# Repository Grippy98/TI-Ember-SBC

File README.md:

# TI-Ember-SBC

[Work in Progress Schematic](TI_Ember_SCH_V00.pdf)

### What is it?

An Arduino Portenta form-factor compatible board based around the Texas Instruments AM625 SiP (System in Package)

### What are the goals of the project?

  * To design a low cost, high performance Arduino Portenta MPU.
  * To help bridge the gap between MCUs and MPUs and create an easy path for projects to migrate to Linux
  * To showcase a 4-6 Layer design that is easily adaptable by the community, open source and built with KiCAD!

### What about software?
  * The board will ship with eMMC pre-flashed with Texas Instruments flavored Debian - traditional Yocto distro will also be available
  * Community engagement is encouraged, and OS Iamges can be flashed or loaded to the on-board eMMC storage or Micro SD Card

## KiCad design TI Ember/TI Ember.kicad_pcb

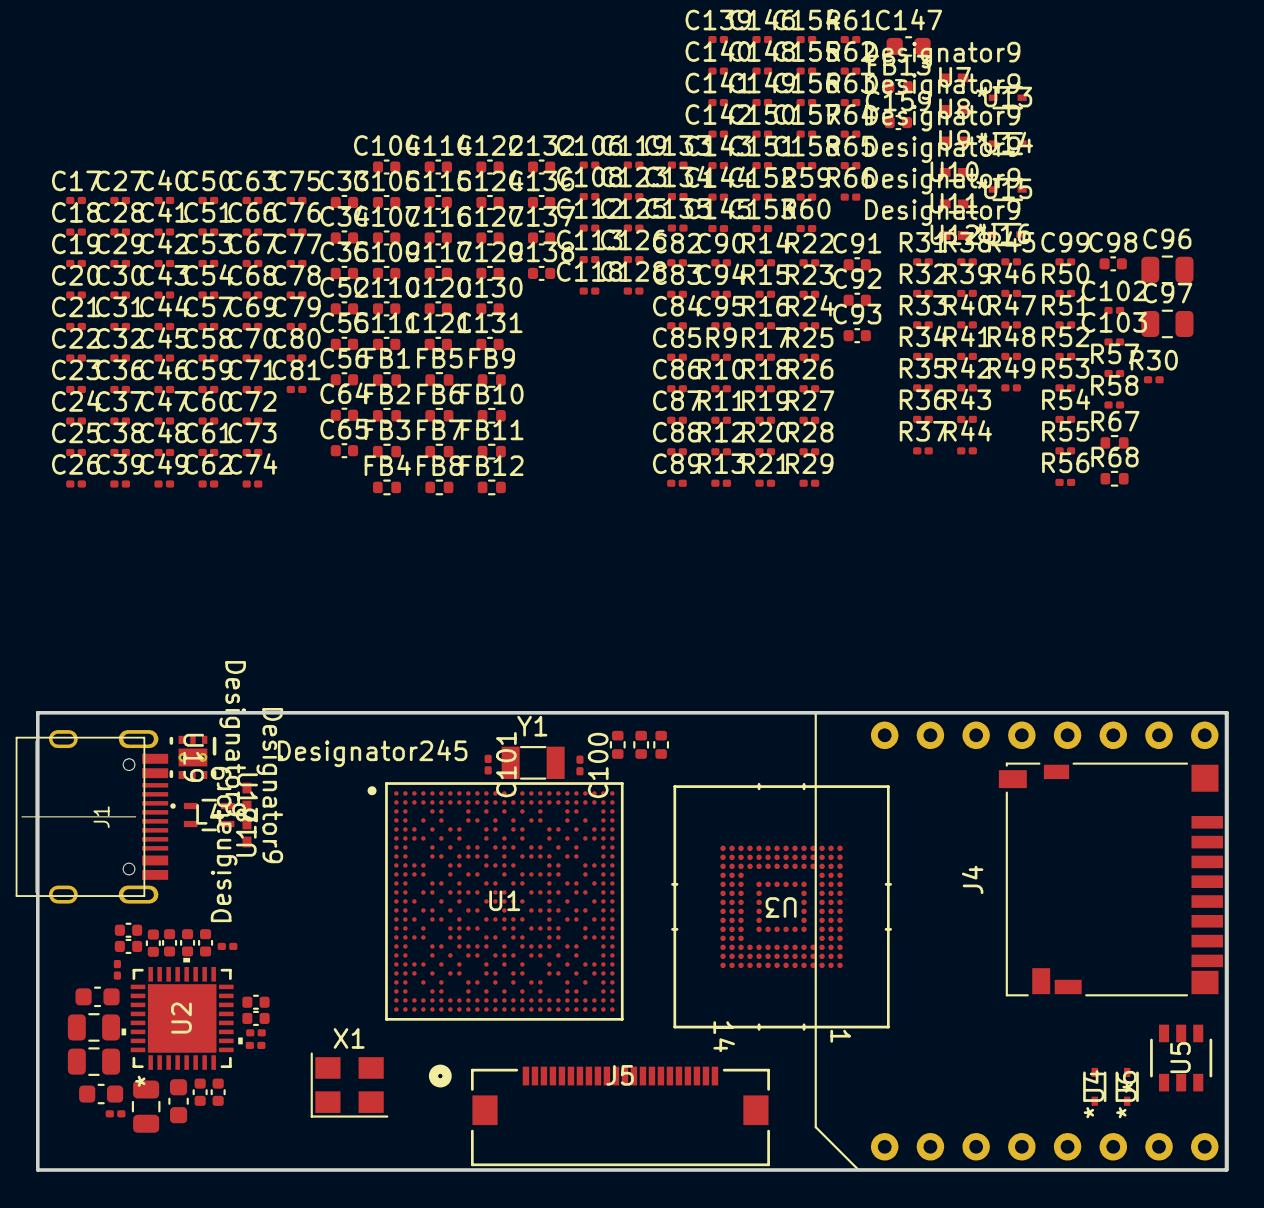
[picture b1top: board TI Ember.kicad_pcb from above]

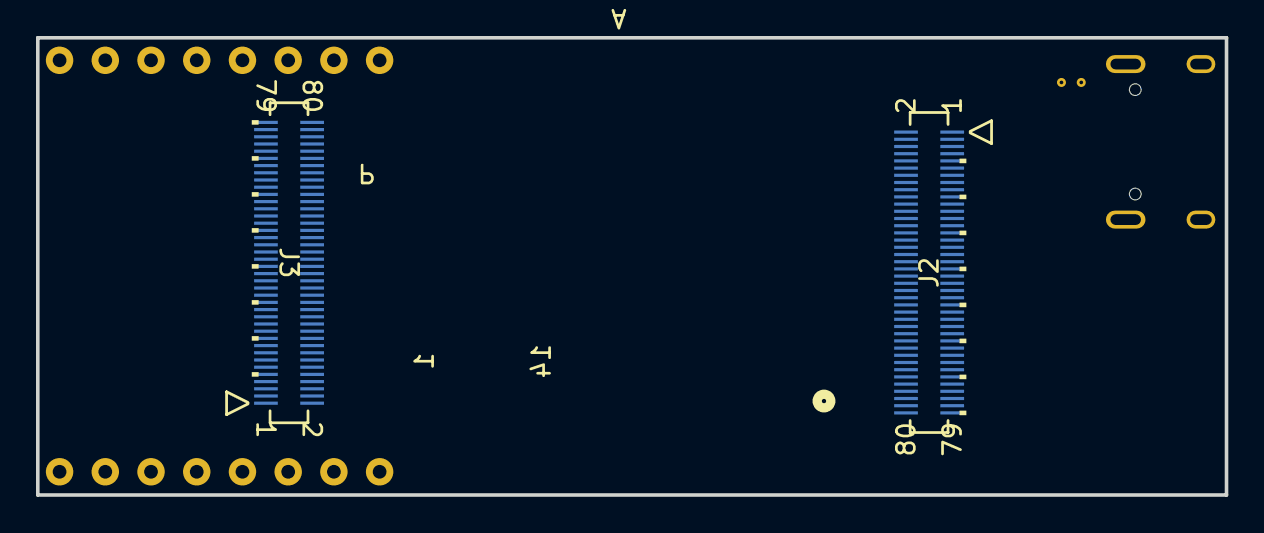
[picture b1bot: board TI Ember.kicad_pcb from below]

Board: 2 copper layers, 66.0 x 25.4 mm, 268 parts (2 on the bottom side), 53 nets, no tracks yet.

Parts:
C1, C2, C3, C4, C7, C8, C10, C11, C14, C16, C159: 2.2uF; C_0402_1005Metric
C5, C6, C9: 10uF; C_0603_1608Metric
C12, C13, C15: 47uF; C_0805_2012Metric
C17, C18, C19, C20, C21, C22, C23, C24, C25, C26, C27, C28, C29, C30, C31, C37, C38, C39, C40, C41, C42, C43, C44, C45, C46, C47, C48, C49, C50, C51, C54, C58, C59, C60, C61, C62, C63, C66, C67, C68, C69, C70, C71, C72, C82, C83, C84, C85, C86, C87, C88, C89, C90, C94, C95, C99, C106, C108, C112, C113, C118, C119, C123, C125, C126, C128, C133, C134, C135, C139, C140, C141, C142, C143, C144, C145, C146, C149, C150, C151, C152, C153, C154, C155, C156, C157, C158: 100nF; C_0201_0603Metric
C32, C36, C53, C57, C73, C74, C75, C76, C77, C78, C79, C80, C81: 1uF; C_0201_0603Metric
C33, C35, C52, C56, C65, C91, C92, C93, C105, C107, C110, C111, C116, C117, C122, C127, C130, C131, C132: 4.7uF; C_0402_1005Metric
C34, C55, C64, C98: 10uF; C_0402_1005Metric
C96, C97: 22uF; C_0805_2012Metric
C100, C101: 20pF; C_0201_0603Metric
C102, C103: 8pF; C_0201_0603Metric
C104, C109, C114, C115, C120, C121, C124, C129, C136, C137, C138: 10nF; C_0402_1005Metric
C147: 22uF; C_0603_1608Metric
C148: 10nF; C_0201_0603Metric
FB1, FB2, FB3, FB4, FB5, FB6, FB7, FB8, FB9, FB10, FB11, FB12, FB13: 120R 1.3A; R_0402_1005Metric
J1: Connector_USB_C_Receptacle_USB2.0; TYPE-C-31-M-12
J2, J3: DF40C-80DP-0.4V51; CONN80_17p5X1p85_hdr_HIR
J4: Micro_SD_Card_Det2; microSD_HC_Hirose_DM3D-SF
J5: 22pin CSI; CONN_54548-2271_MOL
J6: MikroBUS_TH; MkroBUS TH
L4: DLW21SN900HQ2L; IND_DLW21S_0805_MUR
R1, R3: 100K; R_0402_1005Metric
R2: 15K; R_0402_1005Metric
R4, R5, R6, R7, R8, R23, R24, R25, R26, R27, R30, R31, R32, R33, R34, R35, R36, R37, R38, R39, R40, R41, R42, R43, R44, R45, R46, R47, R50, R57, R58, R64: 10K; R_0201_0603Metric
R9, R10, R11, R12, R13, R14, R15, R16, R17, R18, R21, R22: 47K; R_0201_0603Metric
R19, R20, R28: 0R; R_0201_0603Metric
R29: 470K; R_0201_0603Metric
R48, R49, R59, R60, R65: 1K; R_0201_0603Metric
R51: 20K; R_0201_0603Metric
R52, R53, R56: 499R; R_0201_0603Metric
R54, R55: 5.1K; R_0201_0603Metric
R61, R62: 33R; R_0201_0603Metric
R63, R66: DNP; R_0201_0603Metric
R67: DNP; R_0402_1005Metric
R68: 2.2K; R_0402_1005Metric
U1: XAM6254ATCGGAALW; ALW0425A-MFG
U2: TPS6521901RHBR; VQFN32_RHB_TEX
U3: IS21ES08G-JCLI; VFBGA153_ISI-M
U4, U6, U13, U14, U15, U16: RB520S30T1G; SOD-523_0P9X1P3_ONS
U5: TPS22918DBVR; DBV6_TEX
U7, U8, U9, U10, U11, U12, U17, U18: TPD1E10B09DPYR; DPY0002A
U19: TVS0500DRVR; DRV0006A
X1: 25Mhz; Oscillator_SMD_SeikoEpson_SG8002CE-4Pin_3.2x2.5mm
Y1: 32.768kHz; Crystal_SMD_3215-2Pin_3.2x1.5mm

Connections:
DDR_RESET#: R67.2, R68.1
DDR_TEN: R63.2, R65.1
EXTINTn: R8.2, U2.11 (NINT)
GNDREF: C1.2, C2.2, C3.2, C4.2, C5.2, C6.2, C7.2, C8.2, C9.2, C10.2, C11.2, C12.2, C13.2, C14.2, C15.2, C16.2, C17.2, C18.2, C19.2, C20.2, C21.2, C22.2, C23.2, C24.2, C25.2, C26.2, C27.2, C28.2, C29.2, C30.2, C31.2, C32.2, C33.2, C34.2, C35.2, C36.2, C37.2, C38.2, C39.2, C40.2, C41.2, C42.2, C43.2, C44.2, C45.2, C46.2, C47.2, C48.2, C49.2, C50.2, C51.2, C52.2, C53.2, C54.2, C55.2, C56.2, C57.2, C58.2, C59.2, C60.2, C61.2, C62.2, C63.2, C64.2, C65.2, C66.2, C67.2, C68.2, C69.2, C70.2, C71.2, C72.2, C73.2, C74.2, C75.2, C76.2, C77.2, C78.2, C79.2, C80.2, C81.2, C93.2, C94.2, C95.2, C96.2, C97.2, C98.2, C99.2, C100.2, C101.2, C104.2, C105.2, C106.2, C107.2, C108.2, C109.2, C110.2, C111.2, C112.2, C113.2, C114.2, C115.2, C116.2, C117.2, C118.2, C119.2, C120.2, C121.2, C122.2, C123.2, C124.2, C125.2, C126.2, C127.2, C128.2, C129.2, C130.2, C131.2, C132.2, C133.2, C134.2, C135.2, C136.2, C137.2, C138.2, C139.2, C141.2, C142.2, C143.2, C144.2, C145.2, C146.2, C147.2, C149.2, C150.2, C151.2, C152.2, C153.2, C154.2, C155.2, C156.2, C157.2, C158.2, C159.2, J1.A1 (GND), J1.A12 (GND), J1.B1 (GND), J1.B12 (GND), J1.S1 (SHIELD), J6.8 (GND), J6.9 (GND), R2.2, R3.2, R30.2, R50.1, R52.2, R53.2, R54.2, R55.2, R56.2, R60.2, R65.2, R66.2, R68.2, U1.A1 (VSS), U1.A24 (VSS), U1.A25 (VSS), U1.AA11 (VSS), U1.AB9 (VSS), U1.AD1 (VSS), U1.AD9 (VSS), U1.AD12 (VSS), U1.AD16 (VSS), U1.AD25 (VSS), U1.AE1 (VSS), U1.AE8 (VSS), U1.AE12 (VSS), U1.AE16 (VSS), U1.AE24 (VSS), U1.AE25 (VSS), U1.B25 (VSS), U1.F13 (VSS), U1.G13 (VSS), U1.G19 (VSS), U1.H13 (VSS), U1.H16 (VSS), U1.H18 (VSS), U1.H20 (VSS), U1.J7 (VSS), U1.J13 (VSS), U1.K7 (VSS), U1.K13 (VSS), U1.K15 (VSS), U1.K19 (VSS), U1.L20 (VSS), U1.M7 (VSS), U1.M8 (VSS), U1.M10 (VSS), U1.M12 (VSS), U1.M13 (VSS), U1.M17 (VSS), U1.M18 (VSS), U1.N15 (VSS), U1.P7 (VSS), U1.P10 (VSS), U1.P13 (VSS), U1.R13 (VSS), U1.R15 (VSS), U1.R18 (VSS), U1.R20 (VSS), U1.T8 (VSS), U1.T13 (VSS), U1.T14 (VSS), U1.T16 (VSS), U1.T17 (VSS), U1.T18 (VSS), U1.U8 (VSS), U1.U19 (VSS), U1.V9 (VSS), U1.V10 (VSS), U1.V11 (VSS), U1.V13 (VSS), U1.V16 (VSS), U1.V18 (VSS), U1.W7 (VSS), U1.Y2 (VSS), U2.15 (AGND), U2.33 (EPAD), U4.1 (A), U5.2 (GND), U5.3 (ON), U6.1 (A), U17.1 (K), U18.1 (K), U19.1 (GND), U19.2 (GND), U19.3 (GND), U19.7 (PAD)
MCU_PORz: R7.2, U2.18 (NRSTOUT)
unnamed: C104.1, C105.1, C106.1, FB1.2
unnamed: C107.1, C108.1, C109.1, FB9.2
unnamed: C110.1, C112.1, C114.1, FB2.2
unnamed: C111.1, C113.1, C115.1, FB3.2
unnamed: C116.1, C118.1, C120.1, FB4.2
unnamed: C117.1, C119.1, C121.1, FB5.2
unnamed: C122.1, C123.1, C124.1, FB6.2
unnamed: C126.1, FB7.2
unnamed: C127.1, C128.1, C129.1, FB8.2
unnamed: C130.1, C133.1, C136.1, FB10.2
unnamed: C131.1, C134.1, C137.1, FB11.2
unnamed: C132.1, C135.1, C138.1, FB12.2
unnamed: C140.2, C142.1, C143.1, R59.2, R60.1
unnamed: C148.2, R61.2, R62.2
unnamed: C157.1, C158.1, C159.1
unnamed: J1.A5 (CC1), R55.1
unnamed: J1.B5 (CC2), R54.1
unnamed: C93.1, C94.1, C95.1, J4.4 (VDD)
unnamed: R50.2, R51.1
unnamed: C101.1, U1.C2 (WKUP_LFOSC0_XI), Y1.2
unnamed: C100.1, U1.C1 (WKUP_LFOSC0_XO), Y1.1
unnamed: U1.F15 (VDDSHV0), U1.G14 (VDDSHV0)
unnamed: U1.L18 (VDDSHV1), U1.M19 (VDDSHV1)
unnamed: U1.W16 (VDDSHV2), U1.W19 (VDDSHV2)
unnamed: U1.N18 (VDDSHV3), U1.P18 (VDDSHV3), U1.T19 (VDDSHV3), U1.U18 (VDDSHV3)
unnamed: R3.1, U1.J8 (VPP)
unnamed: C73.1, U1.H15 (CAP_VDDS0)
unnamed: C74.1, U1.K18 (CAP_VDDS1)
unnamed: C75.1, U1.W17 (CAP_VDDS2)
unnamed: C76.1, U1.P19 (CAP_VDDS3)
unnamed: C77.1, U1.U7 (CAP_VDDS4)
unnamed: C78.1, U1.H17 (CAP_VDDS5)
unnamed: C79.1, U1.J19 (CAP_VDDS6)
unnamed: C80.1, U1.G9 (CAP_VDDS_CANUART)
unnamed: C81.1, U1.H11 (CAP_VDDS_MCU)
unnamed: U2.2 (LX_B1_1), U2.3 (LX_B1_2)
unnamed: C7.1, U2.14 (VDD1P8)
unnamed: C96.1, U5.5 (QOD), U5.6 (VOUT)
unnamed: C97.1, U5.1 (VIN)
unnamed: J1.A6 (D+), J1.B6 (D+), L4.2, U17.2 (A)
unnamed: J1.A7 (D-), J1.B7 (D-), L4.3, U18.2 (A)
PMIC_LMP_EN0: R5.2, U2.31 (MODE/STBY)
PWR_BTN: R6.2, U2.25 (EN/PB/_VSENSE)
RESETSTATz: U2.28 (MODE/RESET), U4.2 (K)
SD_V_SEL: R4.2, U2.12 (VSEL_SD/_VSEL_DDR)
VBUS: C98.1, C99.1, J1.A4 (VBUS), J1.A9 (VBUS), J1.B4 (VBUS), J1.B9 (VBUS), U19.4 (IN), U19.5 (IN), U19.6 (IN)
VDD: C1.1, C2.1, C3.1, C4.1, C5.1, C6.1, C8.1, C9.1, C10.1, C11.1, C12.1, C13.1, C14.1, C15.1, C16.1, C17.1, C18.1, C19.1, C20.1, C21.1, C22.1, C23.1, C24.1, C25.1, C26.1, C27.1, C28.1, C29.1, C30.1, C31.1, C32.1, C33.1, C34.1, C35.1, C36.1, C37.1, C38.1, C39.1, C40.1, C41.1, C42.1, C43.1, C44.1, C45.1, C46.1, C47.1, C48.1, C49.1, C50.1, C51.1, C52.1, C53.1, C54.1, C55.1, C56.1, C57.1, C58.1, C59.1, C60.1, C61.1, C62.1, C63.1, C64.1, C65.1, C66.1, C67.1, C68.1, C69.1, C70.1, C71.1, C72.1, C125.1, C140.1, C141.1, C144.1, C145.1, C146.1, C147.1, C148.1, C149.1, C150.1, C151.1, C152.1, C153.1, C154.1, C155.1, C156.1, FB1.1, FB2.1, FB3.1, FB4.1, FB5.1, FB6.1, FB7.1, FB8.1, FB9.1, FB10.1, FB11.1, FB12.1, FB13.1, J6.7 (+3.3V), R1.1, R4.1, R5.1, R6.1, R7.1, R8.1, R30.1, R59.1, R63.1, R64.1, R67.1, U1.F11 (VDDSHV_MCU), U1.G7 (VDDS_OSC0), U1.G12 (VDDSHV_MCU), U1.G16 (VDDA_TEMP1), U1.H8 (VDD_CORE), U1.H9 (VDDSHV_CANUART), U1.J11 (VDD_CORE), U1.J12 (VDDR_CORE), U1.J14 (VDD_CORE), U1.K9 (VDDS_DDR), U1.K16 (VDDR_CORE), U1.K17 (VDD_CORE), U1.L8 (VDDS_DDR), U1.L12 (VDD_CORE), U1.L15 (VDD_CORE), U1.M9 (VDDS_DDR_C), U1.M16 (VDD_CORE), U1.N8 (VDD_CORE), U1.N11 (VDD_CORE), U1.N12 (VDDR_CORE), U1.N13 (VDD_CORE), U1.N14 (VDDR_CORE), U1.P9 (VDDS_DDR), U1.P16 (VDDR_CORE), U1.P17 (VDD_CORE), U1.R8 (VDDS_DDR), U1.R11 (VDD_CORE), U1.R12 (VDDR_CORE), U1.R14 (VDD_CORE), U1.T9 (VDDA_TEMP0), U1.T10 (VDDR_CORE), U1.U12 (VDD_CORE), U1.U14 (VDDR_CORE), U1.V8 (VDD_CORE), U1.V15 (VDD_CORE), U1.V17 (VDD_CORE), U2.1 (FB_B1), U2.4 (PVIN_B1_1), U2.5 (PVIN_B1_2), U2.6 (PVIN_LDO1), U2.7 (VLDO1), U2.13 (VSYS), U2.19 (VLDO2), U2.20 (PVIN_LDO2), U2.21 (VLDO3), U2.22 (PVIN_LDO34), U2.23 (VLDO4), U2.24 (FB_B3), U2.26 (PVIN_B3), U2.30 (PVIN_B2), U2.32 (FB_B2)
VDDA_SYS_MON: R1.2, R2.1

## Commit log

2023-06-10 Squashing Commits
